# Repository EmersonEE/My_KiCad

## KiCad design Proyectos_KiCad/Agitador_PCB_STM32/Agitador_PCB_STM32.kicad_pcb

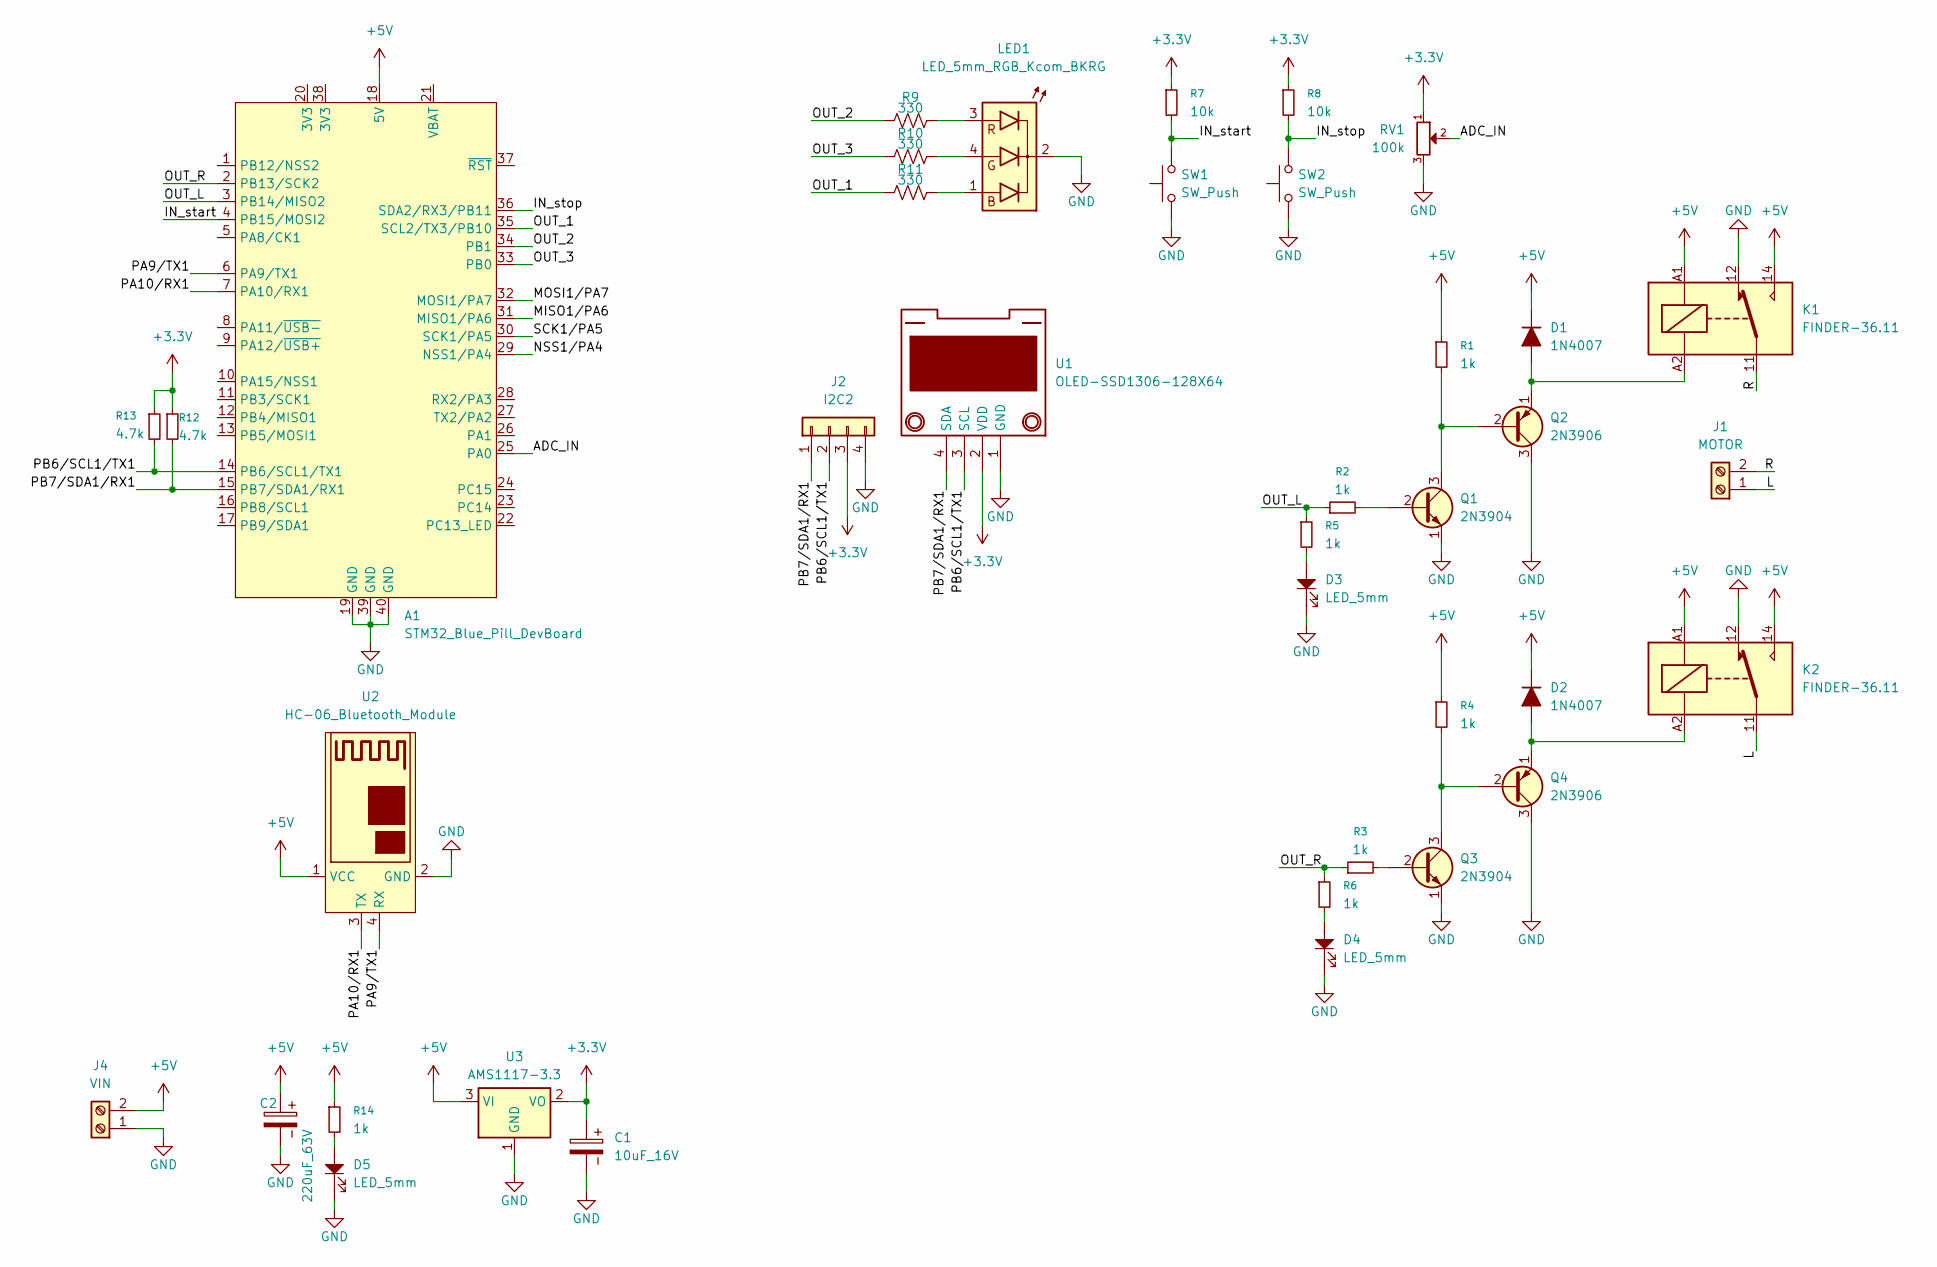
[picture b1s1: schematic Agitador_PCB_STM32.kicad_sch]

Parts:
A1: STM32_Blue_Pill_DevBoard
C1: 10uF_16V; CP_Radial_D5.0mm_P2.00mm
C2: 220uF_63V; CP_Radial_D10.0mm_P5.00mm
D1, D2: 1N4007; D_DO-41_SOD81_P7.62mm_Horizontal
D3, D4, D5: LED_5mm; LED_D5.0mm
J1: MOTOR; TerminalBlock_Phoenix_MKDS-1,5-2-5.08_1x02_P5.08mm_Horizont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
J2: I2C2; PinHeader_1x04_P2.54mm_Vertical
J4: VIN; TerminalBlock_Phoenix_MKDS-1,5-2-5.08_1x02_P5.08mm_Horizont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
K1, K2: FINDER-36.11; Relay_SPDT_Finder_36.11
LED1: LED_5mm_RGB_Kcom_BKRG; LED_D5.0mm-4_RGB_Wide_Pins
Q1, Q3: 2N3904; TO-92_Inline_Wide_EBC
Q2, Q4: 2N3906; TO-92_Inline_Wide_EBC
R1, R2, R3, R4, R5, R6, R14: 1k; 1K
R7, R8: 10k; 10K
R9, R10, R11: 330; R_0805_2012Metric_Pad1.20x1.40mm_HandSolder
R12, R13: 4.7k; 4.7K
RV1: 100k; Potentiometer_Alps_RK163_Single_Horizontal
SW1, SW2: SW_Push; SW_PUSH_6mm
U1: OLED-SSD1306-128X64; PinSocket_1x04_P2.54mm_Vertical
U2: HC-06_Bluetooth_Module
U3: AMS1117-3.3; SOT-223-3_TabPin2

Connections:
+3.3V: C1.1, J2.3, R7.1, R8.1, R12.1, R13.1, RV1.1, U1.2 (VDD), U3.2 (VO)
+5V: A1.18 (5V), C2.1, D1.1 (K), D2.1 (K), J4.2, K1.14, K1.A1, K2.14, K2.A1, R1.1, R4.1, R14.1, U2.1 (VCC), U3.3 (VI)
/ADC_IN: A1.25 (PA0), RV1.2
/IN_start: A1.4 (PB15/MOSI2), R7.2, SW1.2
/IN_stop: A1.36 (SDA2/RX3/PB11), R8.2, SW2.2
/L: J1.1, K2.11
/MISO1/PA6: A1.31 (MISO1/PA6)
/MOSI1/PA7: A1.32 (MOSI1/PA7)
/NSS1/PA4: A1.29 (NSS1/PA4)
/OUT_1: A1.35 (SCL2/TX3/PB10), R11.2
/OUT_2: A1.34 (PB1), R9.2
/OUT_3: A1.33 (PB0), R10.2
/OUT_L: A1.3 (PB14/MISO2), R2.1, R5.1
/OUT_R: A1.2 (PB13/SCK2), R3.1, R6.1
/PA9/TX1: A1.6 (PA9/TX1), U2.4 (RX)
/PA10/RX1: A1.7 (PA10/RX1), U2.3 (TX)
/PB6/SCL1/TX1: A1.14 (PB6/SCL1/TX1), J2.2, R13.2, U1.3 (SCL)
/PB7/SDA1/RX1: A1.15 (PB7/SDA1/RX1), J2.1, R12.2, U1.4 (SDA)
/R: J1.2, K1.11
/SCK1/PA5: A1.30 (SCK1/PA5)
GND: A1.19 (GND), A1.39 (GND), A1.40 (GND), C1.2, C2.2, D3.1, D4.1, D5.1, J2.4, J4.1, K1.12, K2.12, LED1.2 (A), Q1.1 (E), Q2.3 (C), Q3.1 (E), Q4.3 (C), RV1.3, SW1.1, SW2.1, U1.1 (GND), U2.2 (GND), U3.1 (GND)
unnamed: D1.2 (A), K1.A2, Q2.1 (E)
unnamed: D2.2 (A), K2.A2, Q4.1 (E)
unnamed: D3.2, R5.2
unnamed: D4.2, R6.2
unnamed: D5.2, R14.2
unnamed: LED1.1 (B), R11.1
unnamed: LED1.4 (G), R10.1
unnamed: LED1.3 (R), R9.1
unnamed: Q1.2 (B), R2.2
unnamed: Q1.3 (C), Q2.2 (B), R1.2
unnamed: Q3.2 (B), R3.2
unnamed: Q3.3 (C), Q4.2 (B), R4.2

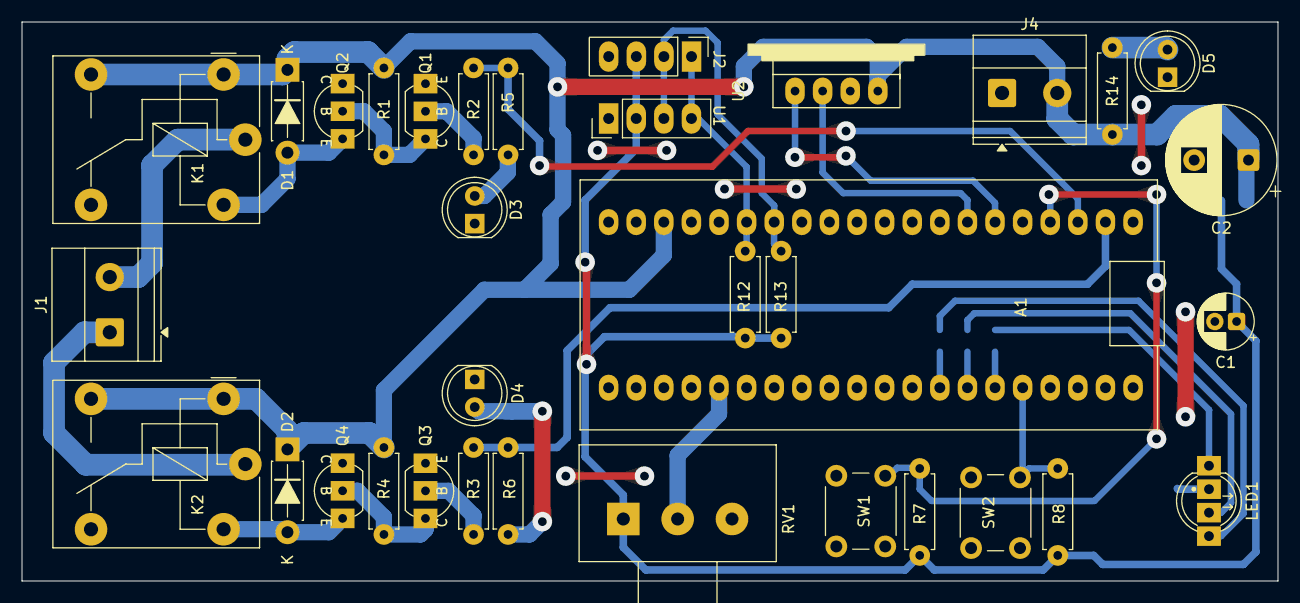
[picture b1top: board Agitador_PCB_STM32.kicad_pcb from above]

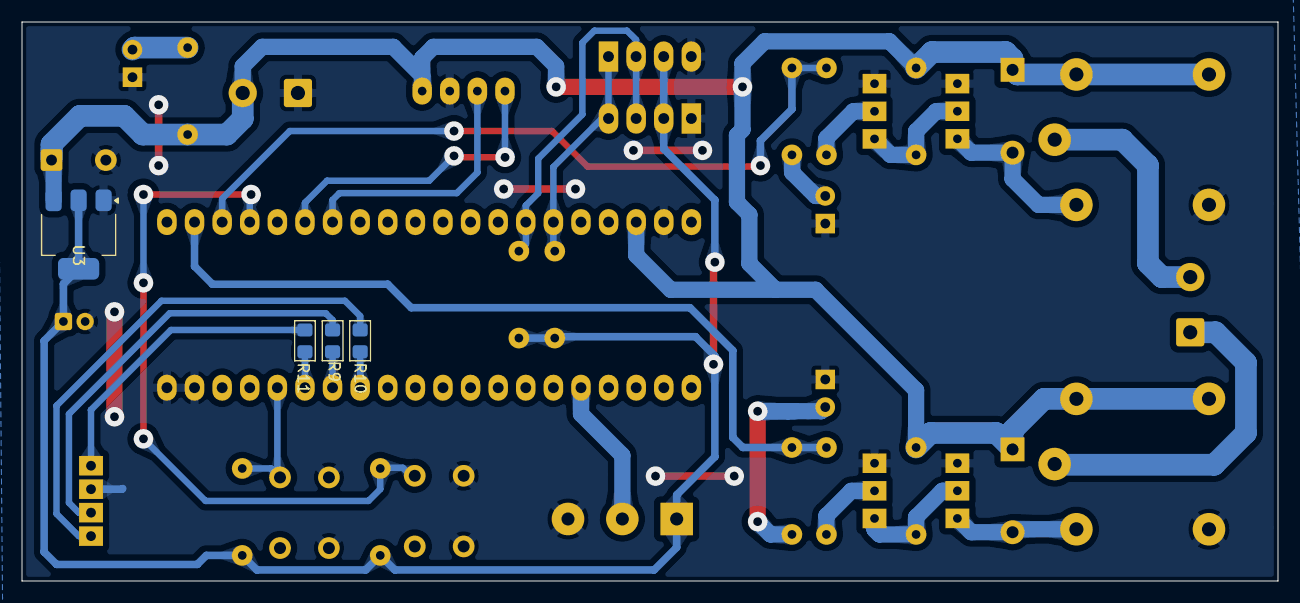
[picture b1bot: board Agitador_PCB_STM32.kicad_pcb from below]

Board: 2 copper layers, 115.6 x 51.4 mm, 38 parts (4 on the bottom side), 29 nets.

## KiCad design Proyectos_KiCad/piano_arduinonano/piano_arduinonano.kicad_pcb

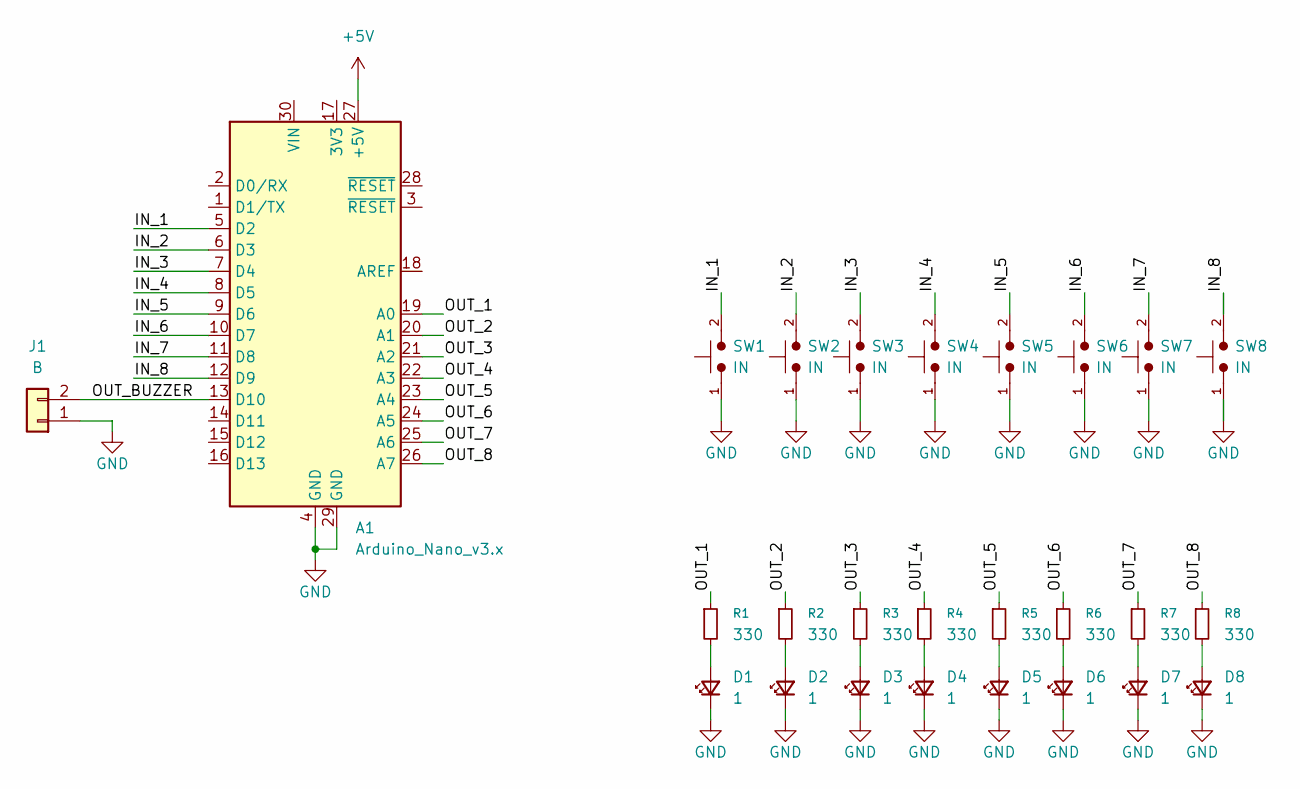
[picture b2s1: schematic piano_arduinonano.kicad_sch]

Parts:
A1: Arduino_Nano_v3.x; Arduino_Nano
D1, D2, D3, D4, D5, D6, D7, D8: 1; LED_D5.0mm
J1: B; Molex_KK-254_AE-6410-02A_1x02_P2.54mm_Vertical
R1, R2, R3, R4, R5, R6, R7, R8: 330; R_Axial_DIN0204_L3.6mm_D1.6mm_P2.54mm_Vertical
SW1, SW5: IN; SW_PUSH-12mmBlue
SW2, SW6: IN; SW_PUSH-12mmGreen
SW3, SW7: IN; SW_PUSH-12mm
SW4, SW8: IN; SW_PUSH-12mmWhite

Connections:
+5V: A1.27 (+5V)
/IN_1: A1.5 (D2), SW1.2
/IN_2: A1.6 (D3), SW2.2
/IN_3: A1.7 (D4), SW3.2
/IN_4: A1.8 (D5), SW4.2
/IN_5: A1.9 (D6), SW5.2
/IN_6: A1.10 (D7), SW6.2
/IN_7: A1.11 (D8), SW7.2
/IN_8: A1.12 (D9), SW8.2
/OUT_1: A1.19 (A0), R1.1
/OUT_2: A1.20 (A1), R2.1
/OUT_3: A1.21 (A2), R3.1
/OUT_4: A1.22 (A3), R4.1
/OUT_5: A1.23 (A4), R5.1
/OUT_6: A1.24 (A5), R6.1
/OUT_7: A1.25 (A6), R7.1
/OUT_8: A1.26 (A7), R8.1
/OUT_BUZZER: A1.13 (D10), J1.2
GND: A1.4 (GND), A1.29 (GND), D1.1 (K), D2.1 (K), D3.1 (K), D4.1 (K), D5.1 (K), D6.1 (K), D7.1 (K), D8.1 (K), J1.1, SW1.1, SW2.1, SW3.1, SW4.1, SW5.1, SW6.1, SW7.1, SW8.1
unnamed: D1.2 (A), R1.2
unnamed: D2.2 (A), R2.2
unnamed: D3.2 (A), R3.2
unnamed: D4.2 (A), R4.2
unnamed: D5.2 (A), R5.2
unnamed: D6.2 (A), R6.2
unnamed: D7.2 (A), R7.2
unnamed: D8.2 (A), R8.2

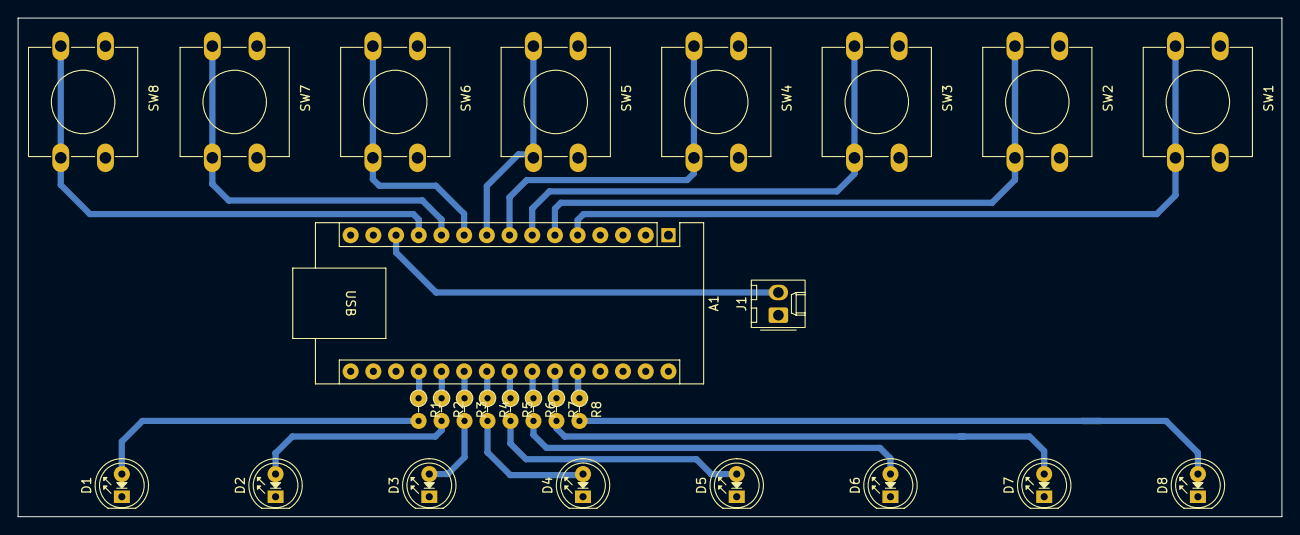
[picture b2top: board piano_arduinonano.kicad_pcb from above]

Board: 2 copper layers, 141.4 x 55.8 mm, 26 parts (0 on the bottom side), 26 nets.

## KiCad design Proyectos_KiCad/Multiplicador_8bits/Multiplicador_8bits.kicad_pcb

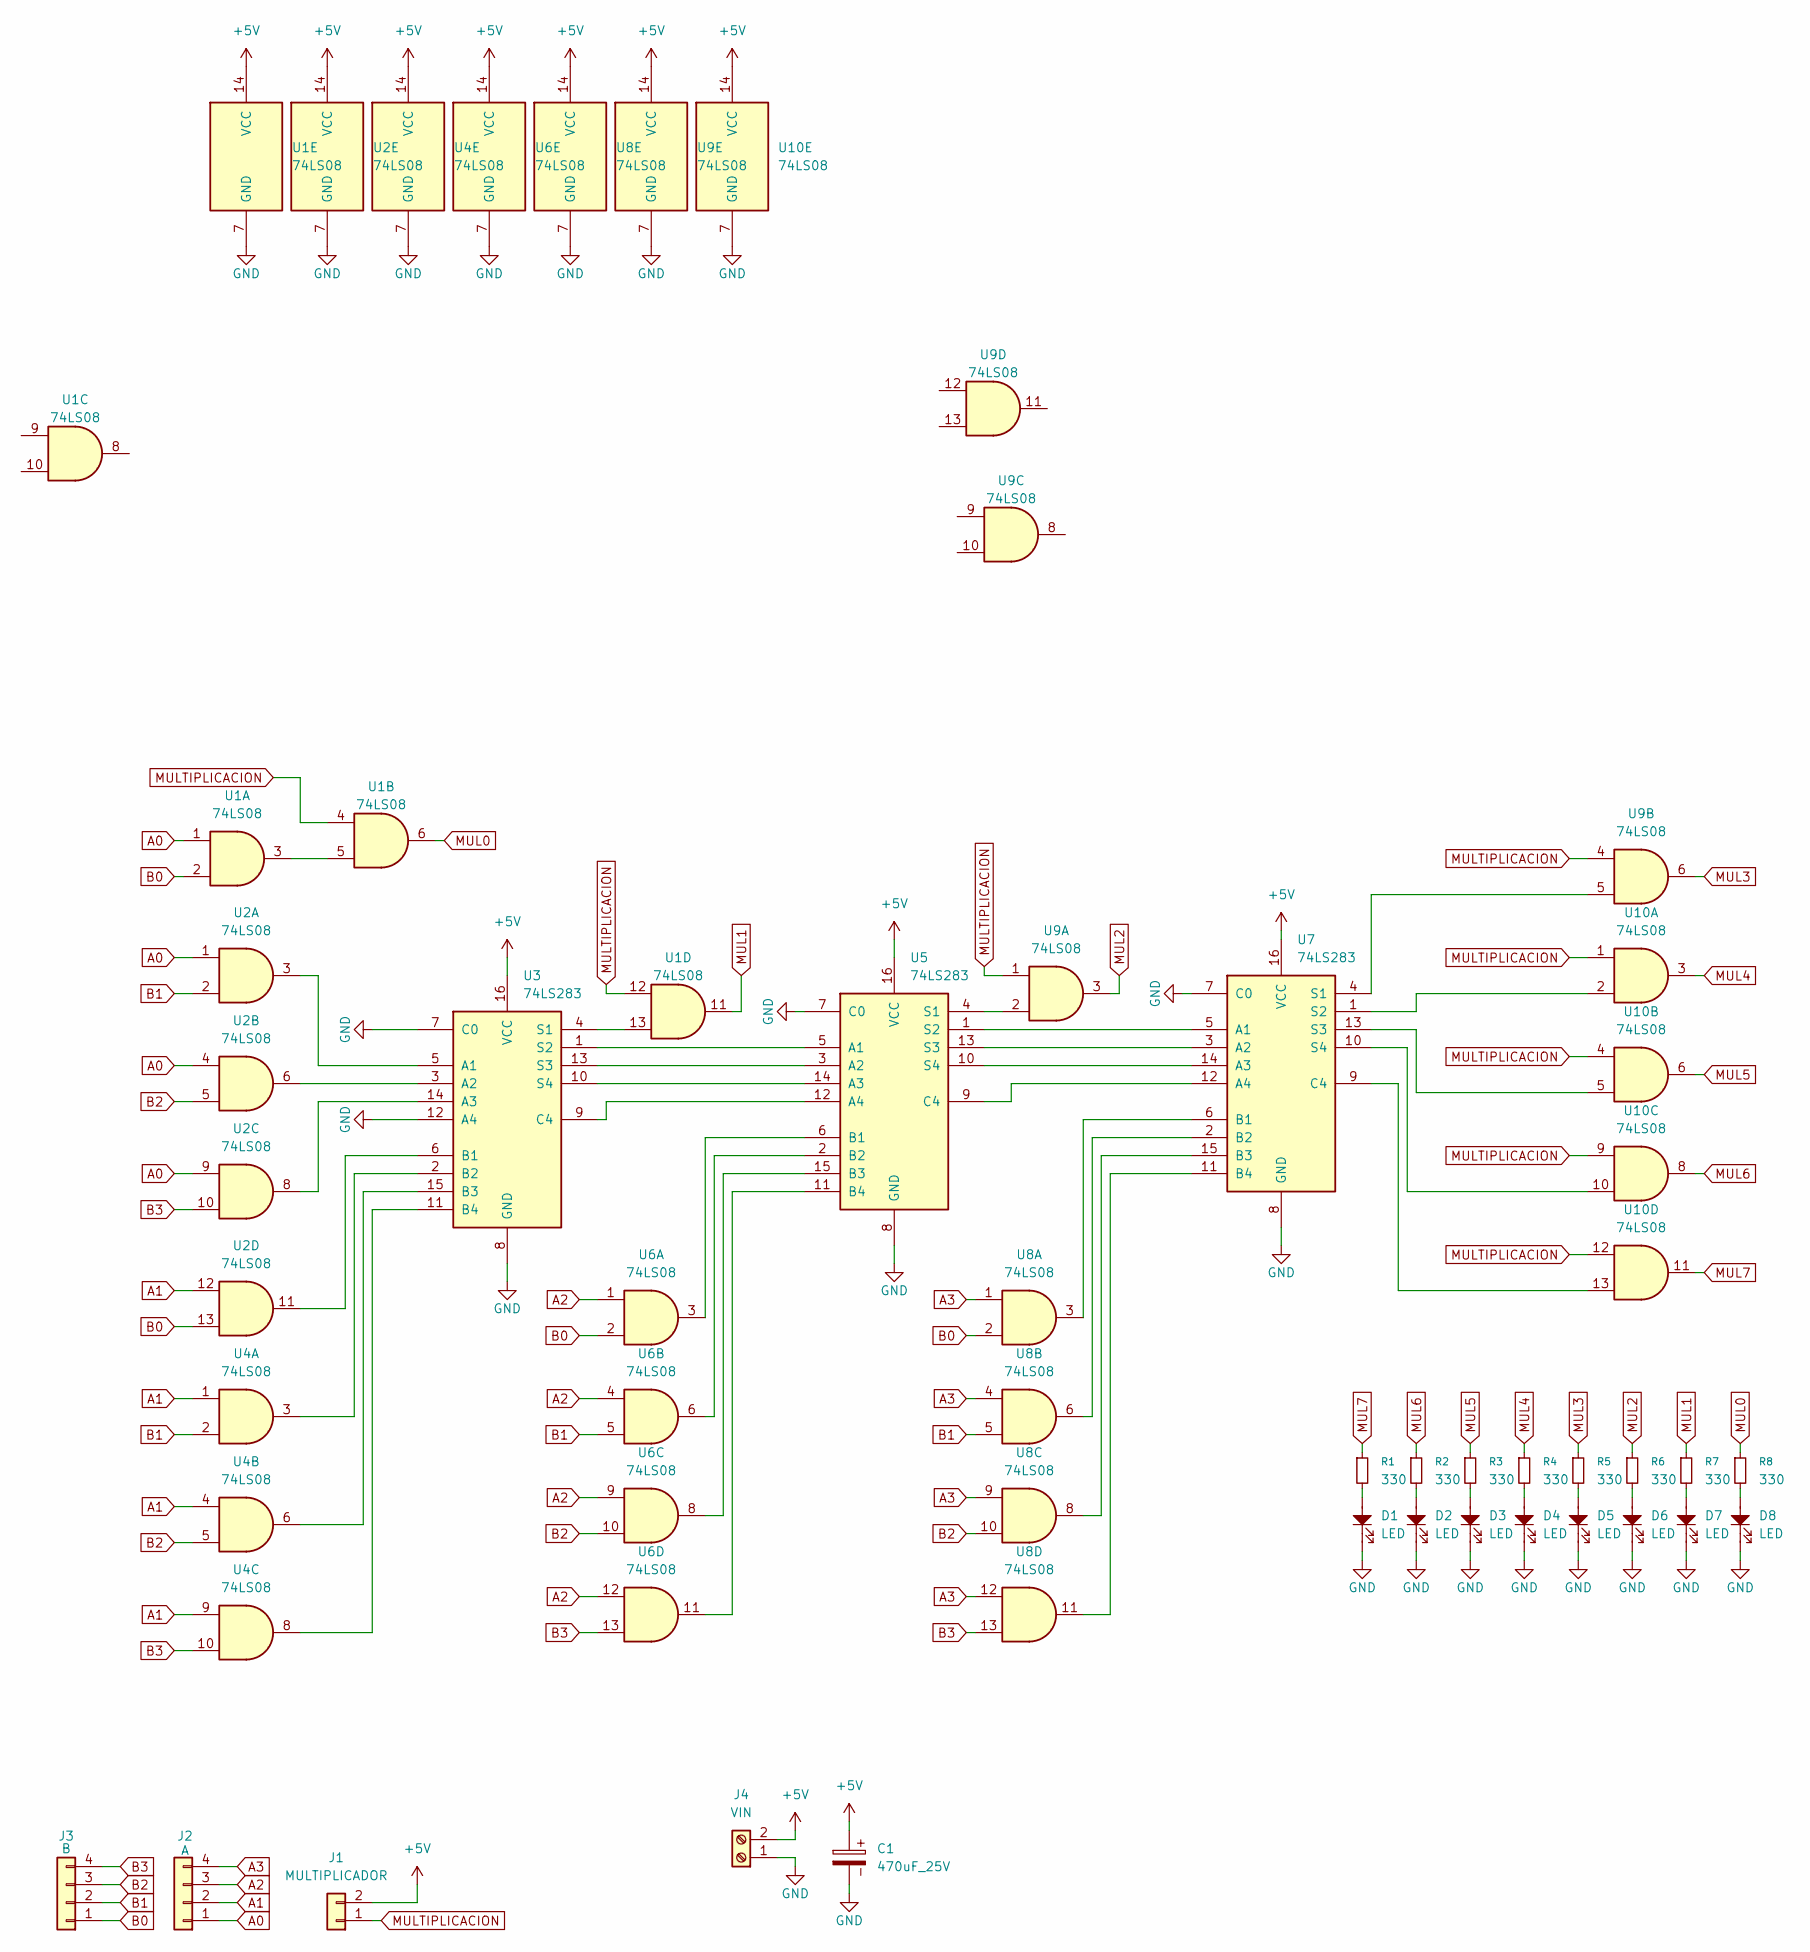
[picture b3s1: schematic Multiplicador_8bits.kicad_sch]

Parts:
C1: 470uF_25V; CP_Radial_D8.0mm_P3.50mm
D1, D2, D3, D4, D5, D6, D7, D8: LED; LED_D5.0mm
J1: MULTIPLICADOR; PinHeader_1x02_P2.54mm_Vertical
J2: A; PinHeader_1x04_P2.54mm_Vertical
J3: B; PinHeader_1x04_P2.54mm_Vertical
J4: VIN; TerminalBlock_Phoenix_MKDS-1,5-2-5.08_1x02_P5.08mm_Horizont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
R1, R2, R3, R4, R5, R6, R7, R8: 330
U1, U2, U4, U6, U8, U9, U10: 74LS08; DIP-14_W7.62mm_LongPads
U3, U5, U7: 74LS283; DIP-16_W7.62mm_LongPads

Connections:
+5V: C1.1, J1.2, J4.2, U1.14 (VCC), U2.14 (VCC), U3.16 (VCC), U4.14 (VCC), U5.16 (VCC), U6.14 (VCC), U7.16 (VCC), U8.14 (VCC), U9.14 (VCC), U10.14 (VCC); also elsewhere on the board
A0: J2.1, U1.1, U2.1, U2.4, U2.9
A1: J2.2, U2.12, U4.1, U4.4, U4.9; also elsewhere on the board
A2: J2.3, U6.1, U6.4, U6.9, U6.12
A3: J2.4, U8.1, U8.4, U8.9, U8.12
B0: J3.1, U1.2, U2.13, U6.2, U8.2
B1: J3.2, U2.2, U4.2, U6.5, U8.5; also elsewhere on the board
B2: J3.3, U2.5, U4.5, U6.10, U8.10; also elsewhere on the board
B3: J3.4, U2.10, U4.10, U6.13, U8.13; also elsewhere on the board
GND: C1.2, D1.1, D2.1, D3.1, D4.1, D5.1, D6.1, D7.1, D8.1, J4.1, U1.7 (GND), U2.7 (GND), U3.7 (C0), U3.8 (GND), U3.12 (A4), U4.7 (GND), U5.7 (C0), U5.8 (GND), U6.7 (GND), U7.7 (C0), U7.8 (GND), U8.7 (GND), U9.7 (GND), U10.7 (GND); also elsewhere on the board
MUL0: R8.1, U1.6
MUL1: R7.1, U1.11, U4.11
MUL2: R6.1, U9.3
MUL3: R5.1, U9.6
MUL4: R4.1, U10.3
MUL5: R3.1, U10.6
MUL6: R2.1, U10.8
MUL7: R1.1, U10.11
MULTIPLICACION: J1.1, U1.4, U1.12, U4.12, U9.1, U9.4, U10.1, U10.4, U10.9, U10.12
unnamed: D1.2, R1.2
unnamed: D2.2, R2.2
unnamed: D3.2, R3.2
unnamed: D4.2, R4.2
unnamed: D5.2, R5.2
unnamed: D6.2, R6.2
unnamed: D7.2, R7.2
unnamed: D8.2, R8.2
unnamed: U1.3, U1.5
unnamed: U2.3, U3.5 (A1)
unnamed: U2.6, U3.3 (A2)
unnamed: U2.8, U3.14 (A3)
unnamed: U2.11, U3.6 (B1)
unnamed 32: U3.2 (B2), U4.3; also elsewhere on the board
unnamed 33: U3.15 (B3), U4.6; also elsewhere on the board
unnamed 34: U3.11 (B4), U4.8; also elsewhere on the board
unnamed: U3.9 (C4), U5.12 (A4)
unnamed: U1.13, U3.4 (S1)
unnamed: U3.1 (S2), U5.5 (A1)
unnamed: U3.13 (S3), U5.3 (A2)
unnamed: U3.10 (S4), U5.14 (A3)
unnamed: U5.6 (B1), U6.3
unnamed: U5.2 (B2), U6.6
unnamed: U5.15 (B3), U6.8
unnamed: U5.11 (B4), U6.11
unnamed: U5.9 (C4), U7.12 (A4)
unnamed: U5.4 (S1), U9.2
unnamed: U5.1 (S2), U7.5 (A1)
unnamed: U5.13 (S3), U7.3 (A2)
unnamed: U5.10 (S4), U7.14 (A3)
unnamed: U7.6 (B1), U8.3
unnamed: U7.2 (B2), U8.6
unnamed: U7.15 (B3), U8.8
unnamed: U7.11 (B4), U8.11
unnamed: U7.9 (C4), U10.13
unnamed: U7.4 (S1), U9.5
unnamed: U7.1 (S2), U10.2
unnamed: U7.13 (S3), U10.5
unnamed: U7.10 (S4), U10.10

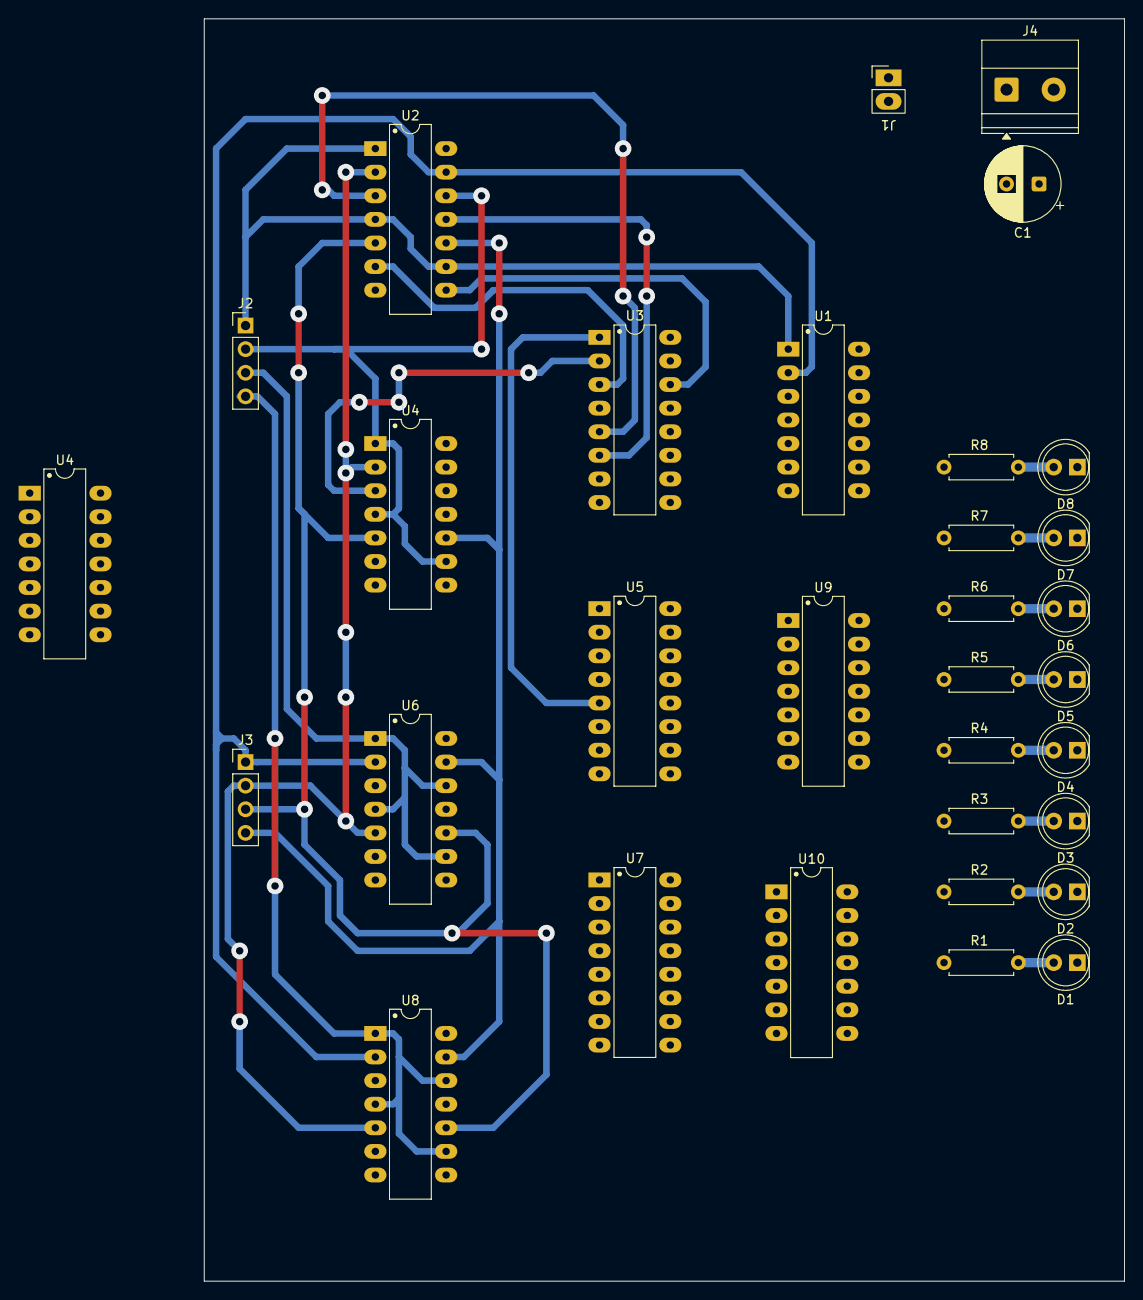
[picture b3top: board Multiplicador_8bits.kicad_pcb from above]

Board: 2 copper layers, 99.1 x 135.9 mm, 32 parts (0 on the bottom side), 58 nets.

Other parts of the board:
U4#2: 74LS08; DIP-14_W7.62mm_LongPads

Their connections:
+5V: U4#2.14 (VCC); also elsewhere on the board
A1: U4#2.1, U4#2.4, U4#2.9; also elsewhere on the board
B1: U4#2.2; also elsewhere on the board
B2: U4#2.5; also elsewhere on the board
B3: U4#2.10; also elsewhere on the board
GND: U4#2.7 (GND); also elsewhere on the board
unnamed 32: U4#2.3; also elsewhere on the board
unnamed 33: U4#2.6; also elsewhere on the board
unnamed 34: U4#2.8; also elsewhere on the board

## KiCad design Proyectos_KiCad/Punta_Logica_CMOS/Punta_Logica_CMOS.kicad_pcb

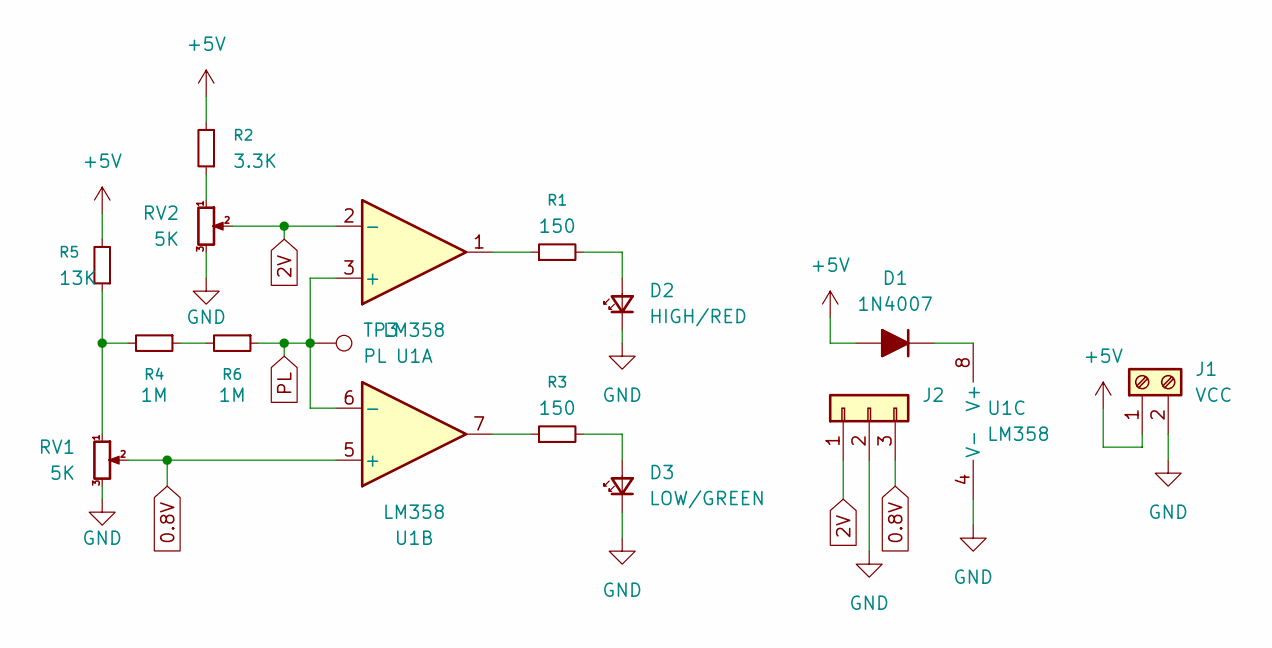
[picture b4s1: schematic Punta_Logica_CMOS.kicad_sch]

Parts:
D1: 1N4007; D_DO-41_SOD81_P7.62mm_Horizontal
D2: HIGH/RED; LED_D5.0mm
D3: LOW/GREEN; LED_G5.0mm
J1: VCC; TerminalBlock_Phoenix_MKDS-1,5-2-5.08_1x02_P5.08mm_Horizont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
J2: PinHeader_1x03_P2.54mm_Vertical
R1, R3: 150
R2: 3.3K; 2.7K
R4, R6: 1M
R5: 13K; 12K
RV1, RV2: 5K; Potentiometer_Runtron_RM-065_Vertical
TP3: PL; PinHeader_1x01_P2.54mm_Vertical
U1: LM358; DIP-8_W7.62mm_LongPads

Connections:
0.8V: J2.3, RV1.2, U1.5 (+)
2V: J2.1, RV2.2, U1.2 (-)
+5V: D1.2 (A), J1.1, R2.2, R5.2
GND: D2.1 (K), D3.1 (K), J1.2, J2.2, RV1.3, RV2.3, U1.4 (V-)
unnamed: D1.1 (K), U1.8 (V+)
unnamed: D2.2 (A), R1.2
unnamed: D3.2 (A), R3.2
unnamed: R1.1, U1.1
unnamed: R2.1, RV2.1
unnamed: R3.1, U1.7
unnamed: R4.1, R6.2
unnamed: R4.2, R5.1, RV1.1
PL: R6.1, TP3.1, U1.3 (+), U1.6 (-)

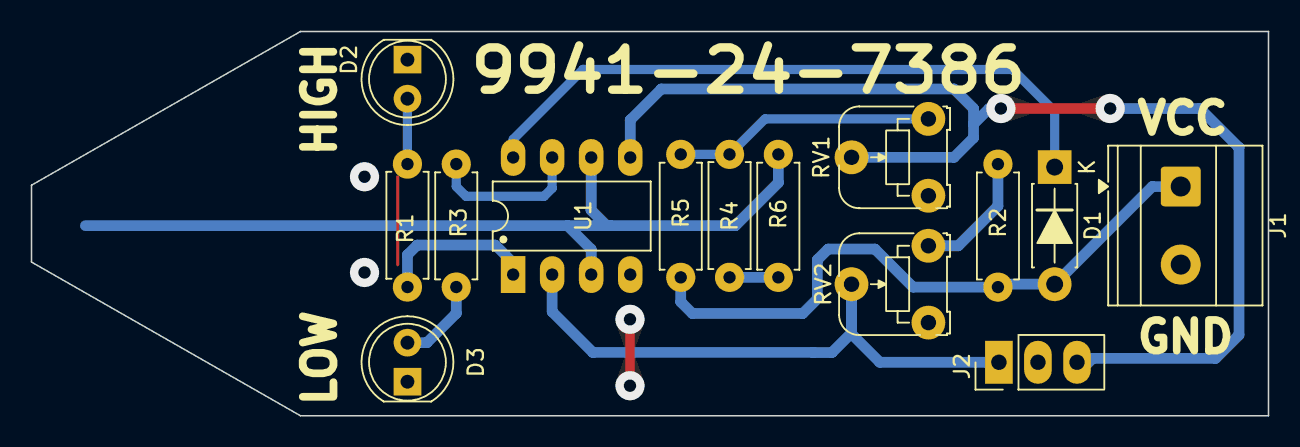
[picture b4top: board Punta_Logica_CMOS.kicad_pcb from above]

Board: 2 copper layers, 80.5 x 25.0 mm, 15 parts (1 on the bottom side), 13 nets.

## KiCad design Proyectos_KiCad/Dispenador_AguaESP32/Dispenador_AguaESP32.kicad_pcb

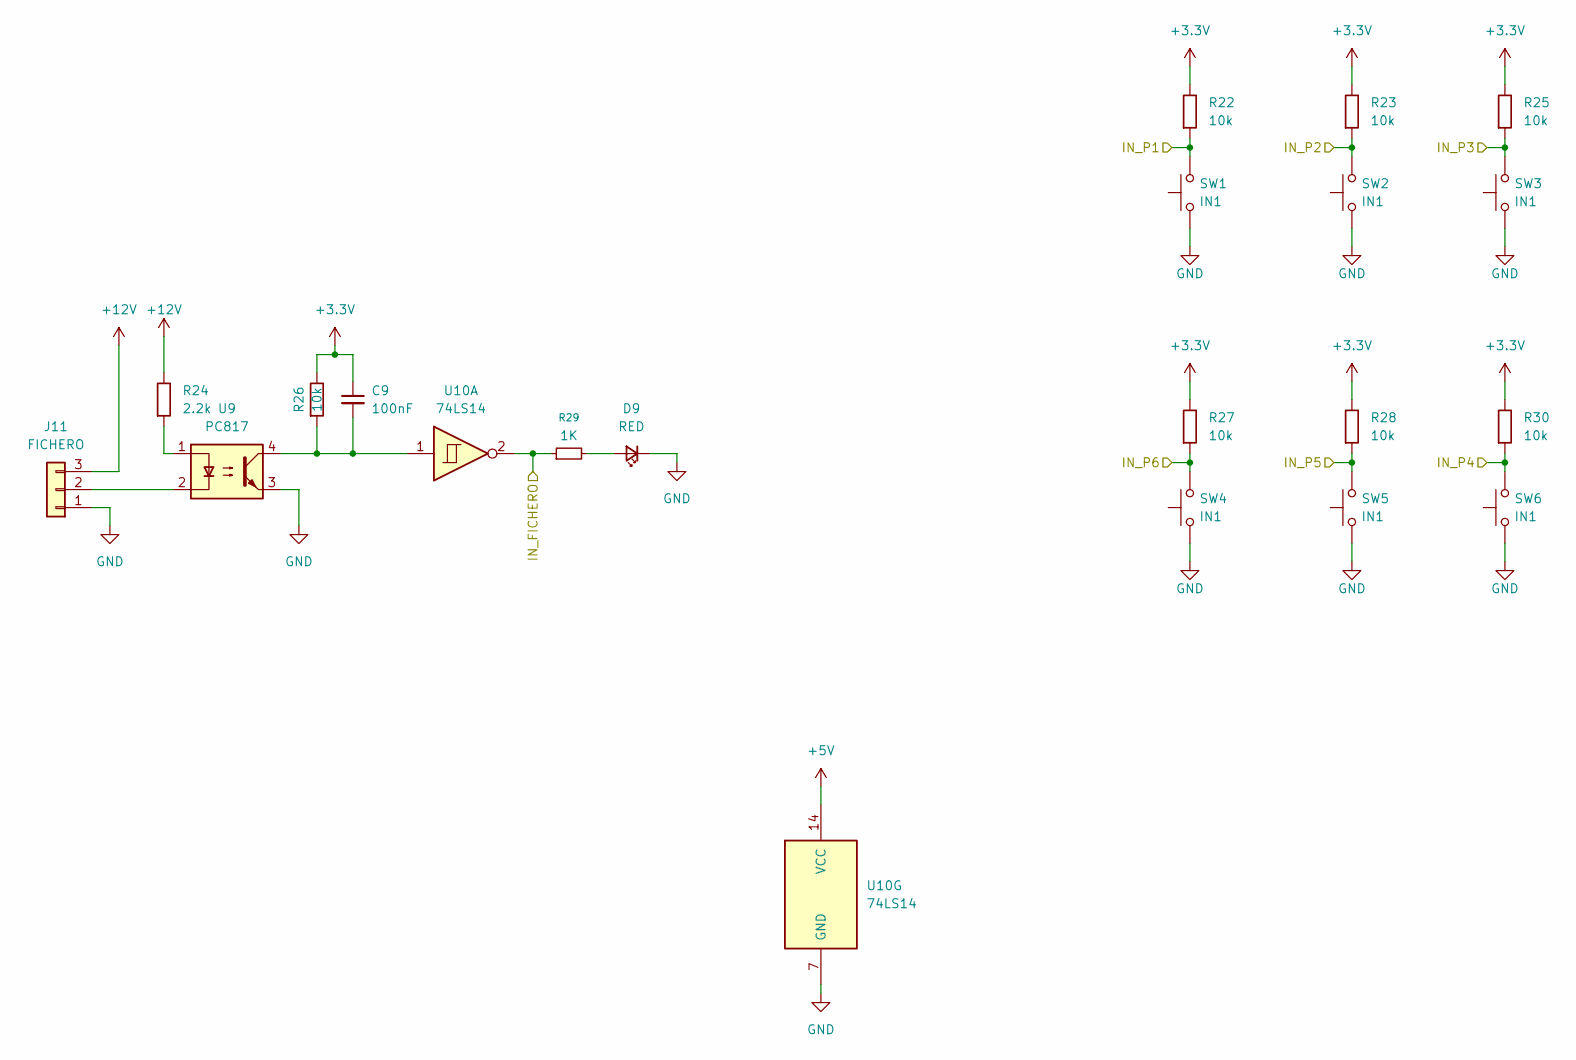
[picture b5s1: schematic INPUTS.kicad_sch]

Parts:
C9: 100nF; C_Disc_D4.3mm_W1.9mm_P5.00mm
D9: RED; LED_D5.0mm
J11: FICHERO; Molex_KK-254_AE-6410-03A_1x03_P2.54mm_Vertical
R22, R23, R25, R26, R27, R28, R30: 10k; 10K
R24: 2.2k; 2.2K
R29: 1K
SW1, SW2, SW3, SW4, SW5, SW6: IN1; Molex_KK-254_AE-6410-02A_1x02_P2.54mm_Vertical; Mfg Part# 8-004 SMD Button 8x3.6mm Height=2.5mm
U9: PC817; DIP-4_W7.62mm
U10: 74LS14; DIP-14_W10.16mm_LongPads

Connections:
+3.3V: C9.1, R22.2, R23.2, R25.2, R26.2, R27.2, R28.2, R30.2; also elsewhere on the board
+5V: U10.14 (VCC); also elsewhere on the board
+12V: J11.3, R24.2; also elsewhere on the board
/ESP32/IN_FICHERO: R29.1, U10.2; also elsewhere on the board
/ESP32/IN_P1: R22.1, SW1.2; also elsewhere on the board
/ESP32/IN_P2: R23.1, SW2.2; also elsewhere on the board
/ESP32/IN_P3: R25.1, SW3.2; also elsewhere on the board
/ESP32/IN_P4: R30.1, SW6.2; also elsewhere on the board
/ESP32/IN_P5: R28.1, SW5.2; also elsewhere on the board
/ESP32/IN_P6: R27.1, SW4.2; also elsewhere on the board
GND: D9.1 (K), J11.1, SW1.1, SW2.1, SW3.1, SW4.1, SW5.1, SW6.1, U9.3, U10.7 (GND); also elsewhere on the board
unnamed: C9.2, R26.1, U9.4, U10.1
unnamed: D9.2 (A), R29.2
unnamed: J11.2, U9.2
unnamed: R24.1, U9.1

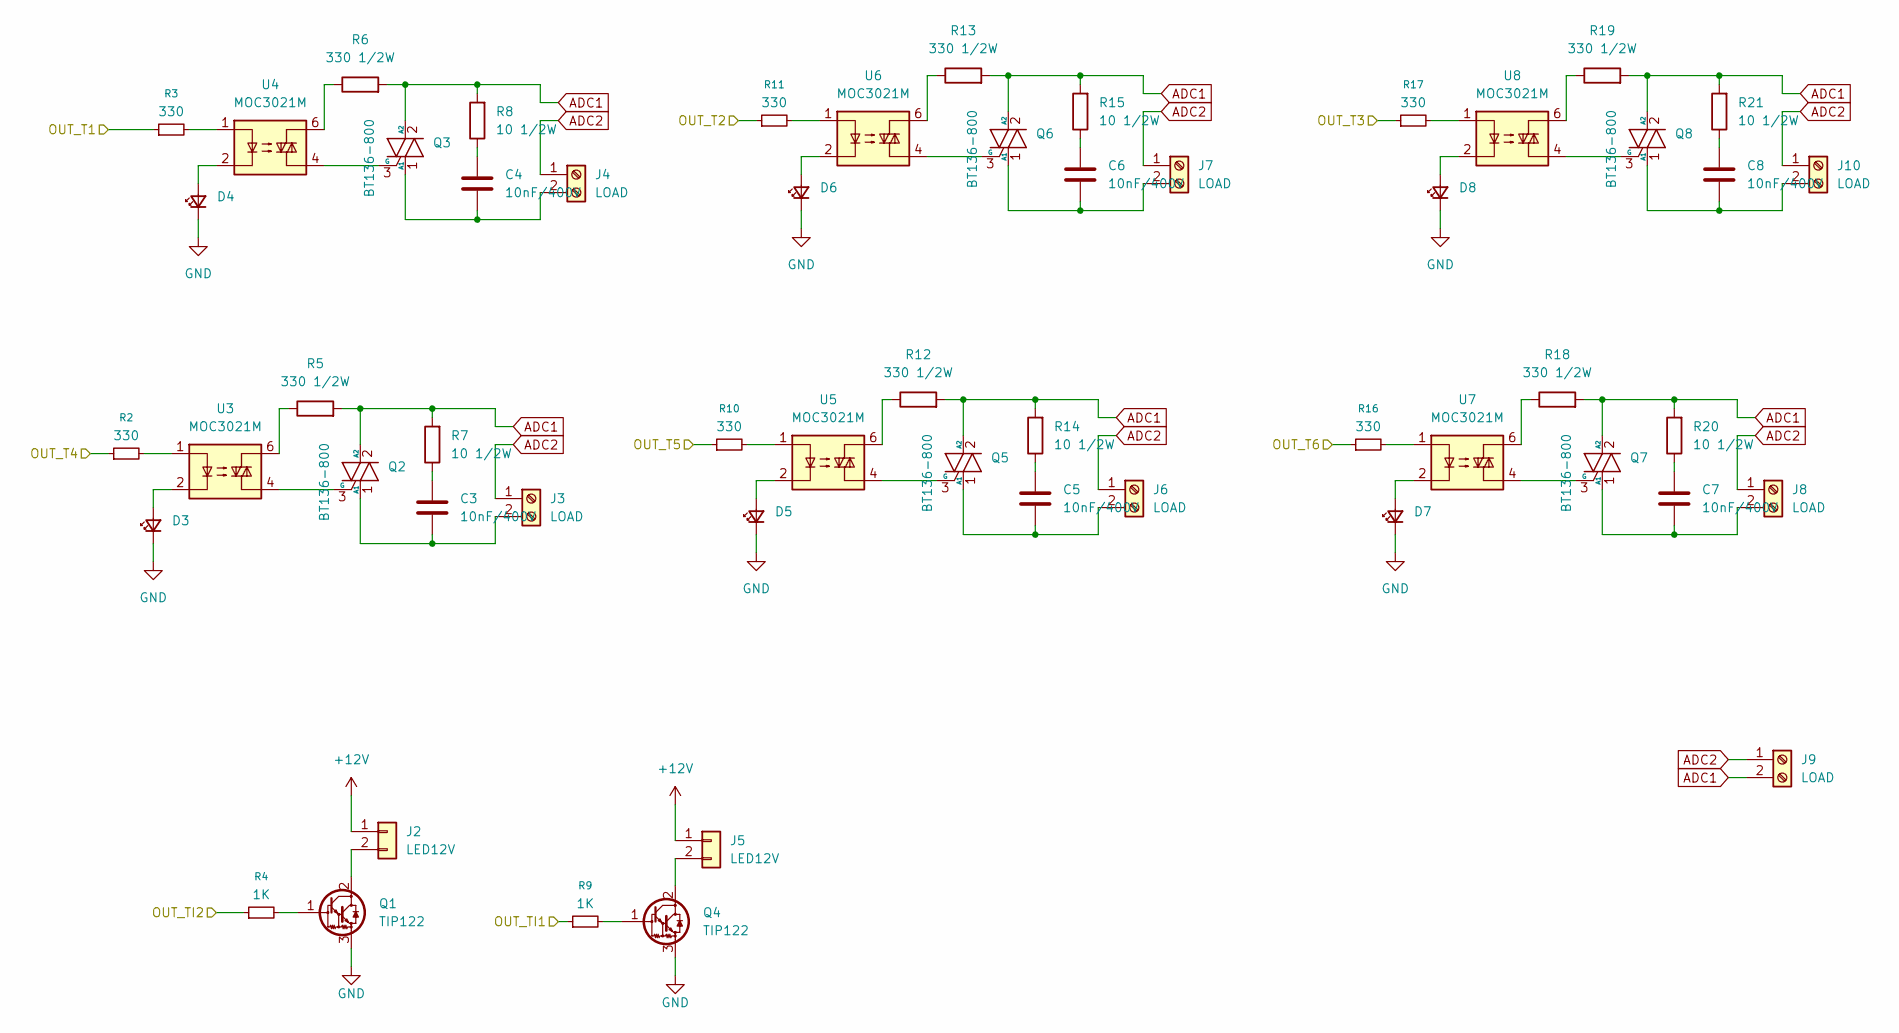
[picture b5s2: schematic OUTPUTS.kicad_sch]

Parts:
C3, C4, C5, C6, C7, C8: 10nF/400V; C_Rect_L13.0mm_W6.0mm_P10.00mm_FKS3_FKP3_MKS4
D3, D4, D5, D6, D7, D8: LED_D5.0mm
J2, J5: LED12V; Molex_KK-254_AE-6410-02A_1x02_P2.54mm_Vertical
J3, J4, J6, J7, J8, J9, J10: LOAD; AMASS_XT30U-F_1x02_P5.0mm_Vertical
Q1, Q4: TIP122; TO-220-3_VDC
Q2, Q3, Q5, Q6, Q7, Q8: BT136-800; TO-220-3_VDC
R2, R3, R10, R11, R16, R17: 330
R4, R9: 1K; 330
R5, R6, R12, R13, R18, R19: 330 1/2W; R_Axial_DIN0207_L6.3mm_D2.5mm_P10.16mm_Horizontal
R7, R8, R14, R15, R20, R21: 10 1/2W; R_Axial_DIN0207_L6.3mm_D2.5mm_P15.24mm_Horizontal
U3, U4, U5, U6, U7, U8: MOC3021M; MOC3020

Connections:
+12V: J2.1, J5.1; also elsewhere on the board
/ESP32/OUT_T1: R3.1; also elsewhere on the board
/ESP32/OUT_T2: R11.1; also elsewhere on the board
/ESP32/OUT_T3: R17.1; also elsewhere on the board
/ESP32/OUT_T4: R2.1; also elsewhere on the board
/ESP32/OUT_T5: R10.1; also elsewhere on the board
/ESP32/OUT_T6: R16.1; also elsewhere on the board
/ESP32/OUT_TI1: R9.1; also elsewhere on the board
/ESP32/OUT_TI2: R4.1; also elsewhere on the board
ADC1: J9.2, Q2.2 (A2), Q3.2 (A2), Q5.2 (A2), Q6.2 (A2), Q7.2 (A2), Q8.2 (A2), R5.2, R6.2, R7.2, R8.2, R12.2, R13.2, R14.2, R15.2, R18.2, R19.2, R20.2, R21.2
ADC2: J3.1, J4.1, J6.1, J7.1, J8.1, J9.1, J10.1
GND: D3.1 (K), D4.1 (K), D5.1 (K), D6.1 (K), D7.1 (K), D8.1 (K), Q1.3 (E), Q4.3 (E); also elsewhere on the board
unnamed: C3.1, R7.1
unnamed: C4.1, R8.1
unnamed: C5.1, R14.1
unnamed: C6.1, R15.1
unnamed: C7.1, R20.1
unnamed: C8.1, R21.1
unnamed: D3.2 (A), U3.2
unnamed: D4.2 (A), U4.2
unnamed: D5.2 (A), U5.2
unnamed: D6.2 (A), U6.2
unnamed: D7.2 (A), U7.2
unnamed: D8.2 (A), U8.2
unnamed: J2.2, Q1.2 (C)
unnamed: C3.2, J3.2, Q2.1 (A1)
unnamed: C4.2, J4.2, Q3.1 (A1)
unnamed: J5.2, Q4.2 (C)
unnamed: C5.2, J6.2, Q5.1 (A1)
unnamed: C6.2, J7.2, Q6.1 (A1)
unnamed: C7.2, J8.2, Q7.1 (A1)
unnamed: C8.2, J10.2, Q8.1 (A1)
unnamed: Q1.1 (B), R4.2
unnamed: Q2.3 (G), U3.4
unnamed: Q3.3 (G), U4.4
unnamed: Q4.1 (B), R9.2
unnamed: Q5.3 (G), U5.4
unnamed: Q6.3 (G), U6.4
unnamed: Q7.3 (G), U7.4
unnamed: Q8.3 (G), U8.4
unnamed: R2.2, U3.1
unnamed: R3.2, U4.1
unnamed: R5.1, U3.6
unnamed: R6.1, U4.6
unnamed: R10.2, U5.1
unnamed: R11.2, U6.1
unnamed: R12.1, U5.6
unnamed: R13.1, U6.6
unnamed: R16.2, U7.1
unnamed: R17.2, U8.1
unnamed: R18.1, U7.6
unnamed: R19.1, U8.6
